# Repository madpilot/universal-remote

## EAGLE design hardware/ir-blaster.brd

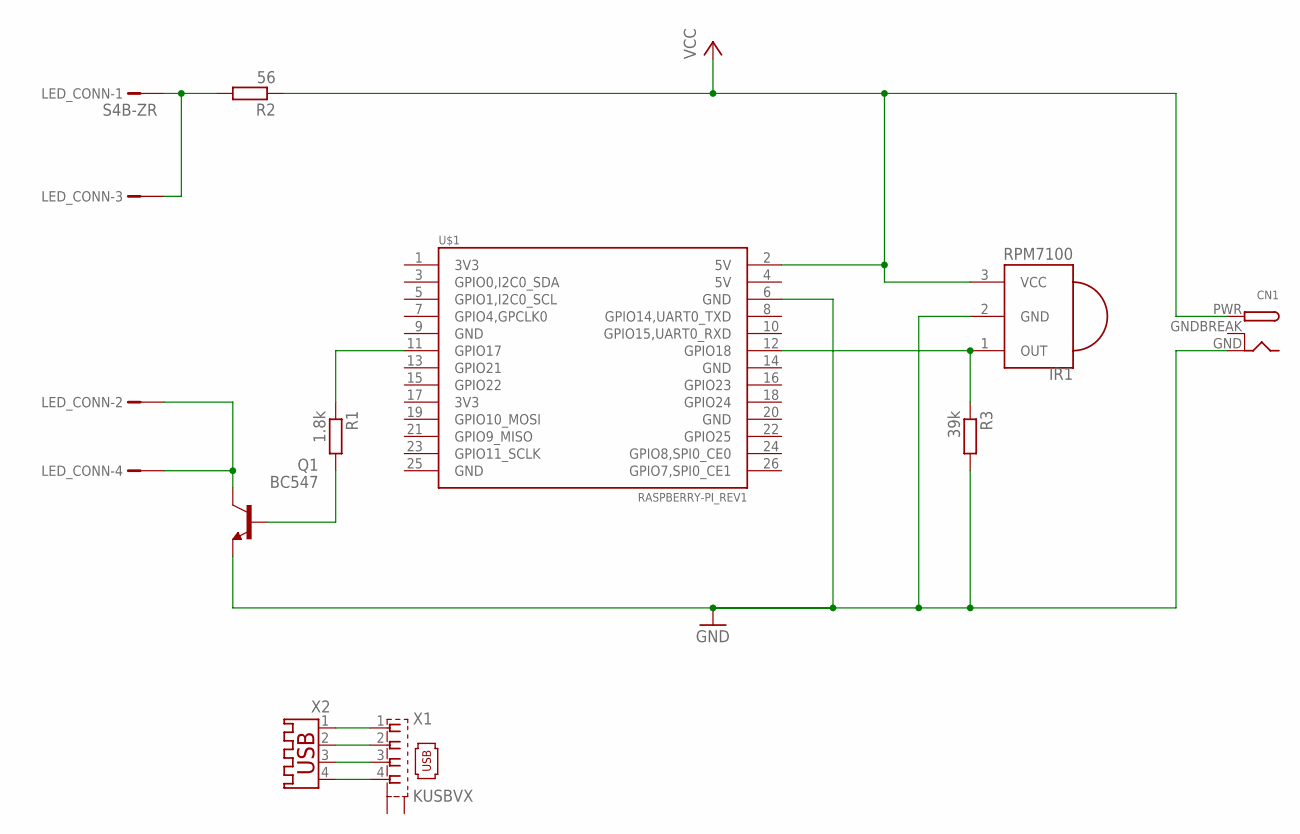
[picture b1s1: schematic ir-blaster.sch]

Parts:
CN1: DCBARRELPTH; DCJACK_2MM_PTH
IR1: RPM7100; PNA460XM
LED_CONN: S4B-ZR
Q1: BC547; TO92
R1: 1.8k; 0207/10
R2: 56; 0207/10
R3: 39k; 0207/10
U$1: RASPBERRY-PI_REV1
X1: KUSBVX
X2: USB-A003

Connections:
GND: CN1.GND, IR1.2 (GND), Q1.1 (E), R3.2, U$1.6 (GND)
GNDBREAK: CN1.GNDBREAK
unnamed: LED_CONN.1, LED_CONN.3, R2.2
unnamed: LED_CONN.2, LED_CONN.4, Q1.3 (C)
unnamed: X1.1, X2.1
unnamed: X1.2, X2.2
unnamed: Q1.2 (B), R1.2
unnamed: R1.1, U$1.11 (GPIO17)
unnamed: IR1.1 (OUT), R3.1, U$1.12 (GPIO18)
unnamed: X1.3, X2.3
unnamed: X1.4, X2.4
VCC: CN1.PWR, IR1.3 (VCC), R2.1, U$1.2 (5V)

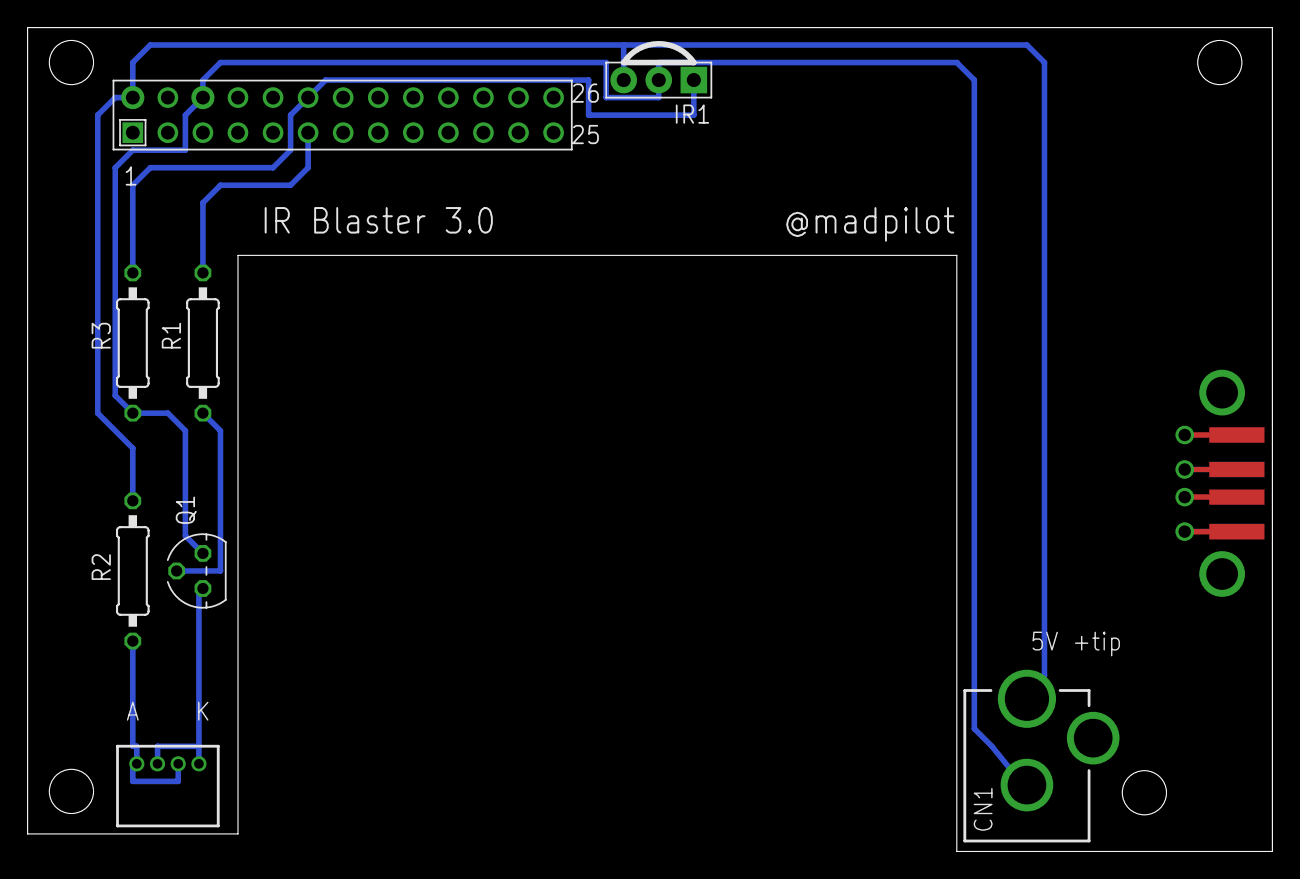
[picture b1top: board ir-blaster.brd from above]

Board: 2 copper layers, 90.2 x 59.7 mm, 10 parts (0 on the bottom side), 11 nets.

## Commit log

2016-01-13 Checking in boards
2016-09-18 Redesigning board so it fits on top of the PI properly
2016-12-05 Building basic device factory
2016-12-05 adding basic http server input
2016-12-05 Adding basic error handling, adding logging
2016-12-05 Logging errors in HTTP Input
2016-12-05 Improving error messages
2016-12-06 adding documents around remote codes
2016-12-06 Adding devices endpoint
2016-12-06 Wrote script to pull codes from CSV
2016-12-07 Adding concept of subscribers, so we can feel back state we read from CEC
2016-12-07 Setting up lirc autodiscovery
2016-12-07 LIRC devices are auto-discovered
2016-12-07 Improving error handling
2016-12-11 Starting work on virtuals
2016-12-12 Adding case STL
2016-12-13 STarting to add CEC stuff
2016-12-13 implementing send, sendstart and sendstop
2016-12-13 CEC changes now run
2016-12-14 CEC works
2016-12-15 Allowing injection of custom scripts to override broken CEC implementations
2017-01-26 Adding support for different winston loggers, moving config.json to config.sample.json
2017-01-26 Adding bin to package.json
2017-01-26 Adding options parser
2017-01-26 Use absolute paths for custom overrides
2017-01-26 Adding a dummy output device for testing
2017-01-27 Adding support for an apiKey
2017-01-28 Building in SSL support
2017-02-26 Revision 3. Moved the LEDs off board onto wires
2017-02-26 Flipping board, so screw holes align of three of the four corners
2017-02-26 Adjusted screw hold position to match ethernet port holes. Reduced width of board so USB network adapter will fit. Adjusted labels to fit on board
2017-02-26 Getting correct measurements for holes. Making the board cover the whole PI again. Added measurement markers for the USB WIFI dongle. Need to make up a custom pad for that
2017-02-27 Adding pads for the USB wifi dongle
2017-06-03 Working on version 3 of the board
2017-06-03 Adding yarn.local
2017-07-16 Removing node server
2017-07-16 Adding a basic phoenix application, and a readme file explaining what is going on
2017-07-16 Setting up the different apps that will be needed
2017-07-20 Adding device and code mappers
2017-07-20 Adding control specs
2017-07-20 Adding tests for reserved
2017-07-23 Basic Genserver sending and receiving data from STDIO
2017-07-23 Using the GenStage module to setup a event bus
2017-07-24 Setup a supervisor trewe with a process and a Genstage producer. Wired up a consumer to test
2017-07-24 Using the BroadcastDispatcher strategy, as the producer is probably the bottle neck
2017-07-24 Cleaning up the Producer init function
2017-07-24 Removing hardcoded executable
2017-07-24 face client captures SIGPIPE
2017-07-25 Testing CEC.Process
2017-07-25 Fixing device identifies, as they are actually only 1 byte, not two
2017-07-26 Starting to implement some command composition
2017-07-26 Adding on_touch_play library
2017-07-26 Adding one_touch_record vanity functions
2017-07-26 Adbstracting away a generic mapper for code translation
2017-07-26 Adding system standby commands
2017-07-26 Adding remote control passthrough
2017-07-27 Adding device menu control
2017-07-27 Adding specs for menu request, status and record error mappings
2017-07-27 Adding audio status
2017-07-27 Adding deck
2017-07-27 Adding deck tests
2017-07-27 Adding in best guess for record on
2017-07-27 Updating readme to better represent where things are going. Not implemented yet though
2017-07-31 Implementing system info
2017-07-31 Using device mappings for report_phsyical_address
2017-07-31 Adding OSD functions
2017-08-02 Adding opcode mappings
2017-08-04 Spliting up source and destination mapping, so parser works correctly
2017-08-04 Renaming opcode -> command, as we'll use that for lirc too
2017-08-04 Started to add argument parsing. needs refactoring
2017-08-05 Mapping abort codes
2017-08-05 Starting to work through testing argument parsers
2017-08-05 Adding more parsers
2017-08-05 Setting up pending test, adding some more parsers
2017-08-05 Testing no argument operands
2017-08-05 More parsers
2017-08-06 Adding parses for audio rate, testing more mapping
2017-08-06 Adding more mapping specs
2017-08-07 Adding a samsung conf, updating the foxtel conf to real values
2017-08-07 Correct foxtel codes
2017-08-08 Adding LIRC setup
2017-08-08 Testing list_devices and list_commands
2017-08-08 Testing send_command
2017-08-09 Putting in specs for op_codes
2017-08-09 Removing phoenix
2017-08-09 Removing the rest of the phoenix config
2017-08-09 Adding plug
2017-08-09 Adding bus command to the packet
2017-08-09 Simple TCP socket. Needs work
2017-08-10 Proof of concept
2017-08-10 Listening to LIRC and CEC bus
2017-08-11 Setting up a remote behaviour that any remote control can implement
2017-08-11 Faking LIRC. Triming output to remove nil objects, adjusting web api to send correct commands, adding a remote behaviour
2017-08-11 Refactoring web api
2017-08-11 ADding a remotes state to maintain a dynamic list of remote controls
2017-08-12 Making naming of remote senders consistant with LIRC, add test for LIRC.remote
2017-08-12 Adding some remote specs
2017-08-13 Testing send commands on CEC remote
2017-08-13 Testing Remotes list
2017-08-13 Testing proxies
2017-08-13 Adding error if a device does not exist for CEC
2017-08-14 Adding key validity check
2017-08-14 Changing error tuple
2017-08-14 More tests on web server
2017-08-15 Using the elixir config system for configuration. Removing json file
2017-08-15 Moving configuration details to correct place, adding some logging
2017-08-15 removing a warning
2017-08-15 Fixing a typo
2017-08-15 Adding more logs
2017-08-17 Adding devices gen_server which can load scripts
2017-08-19 irsend outputs to STDERR in real life
2017-08-19 Working on schema
2017-08-19 Not worrying about config just yet. Cleaned up webserver initialization
2017-08-19 Adding basic process termination
2017-08-23 Adding some tests for devices
2017-08-23 Making commands an actual array
2017-08-26 Adding handler loader
2017-08-27 Refactoring devices to allow send_once, send_start and send_stop
2017-09-10 Need to change the DSL slightly
2017-09-12 Adding tests to the DSL
2018-05-03 Adding status and listeners
2018-05-03 Fixing the filter code
2018-05-03 Testing Bus.wait_for
2018-05-04 Adding status end point
2018-05-04 Rolling back cowboy to verions 1.1.2
2018-05-04 Adding a /status endpoint that returns all possible statuses for a device
2018-05-04 Adding statuses and metadata to /devices/:device
2018-05-04 Supporting CEC version 1.4
2018-05-05 removing ssl, because the RAspberry PI B struggles
2018-05-05 Adding a logger file backend for production
2018-05-06 Moving to a separate bus
2018-05-06 Adding seperate bus. Using receive to sleep the Device - this is literally designed to do what I was hacking around. Extracting the listener, so device can just become a GenServer that delegates bus 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
2018-05-06 Killing the OneShotListener on event timeout
2018-05-07 Bus listener is broker
2018-05-07 Fixing the return result
2018-05-11 Enable fakecec to respond to volume requests
2018-05-19 Adjusting the Listener test
2018-05-19 Testing partial and complete matches
2018-05-19 Testing event listener filter
2018-05-20 Adding an event bus
2018-05-20 Trying again with the unified Bus concept
2018-05-20 Adding some debug to the bus event handler
2018-05-20 Setting up websocket code
2018-05-20 Refactoring device actions out to an API, so websockets can call them too
2018-05-20 Using the new devices API for websockets
2018-05-20 Reformatting
2018-05-20 Adding additional invormation to API responses, so they are more easily identified
2018-05-20 Normalizing the status response
2018-05-20 Adjusting tests to deal with new payload shap. Renaming list_actions to get_metadata
2018-05-20 Fixing a test
2018-05-20 Atomising further up the change, so the API doesn't have to do it
2018-05-20 Abstracting remotes to an API object. Making the API more structured
2018-05-21 Changing top-level bus attribute to channel, to stop clash with the remotes API
2018-05-21 Removing the bus, because it doesn't seem to start listigin properly
2018-05-21 removing some APex.aps
2018-05-21 Gracefully handling bad atom conversion
2018-05-21 Only atomising params is they are strings
2018-05-21 Caching lirc atoms on startup so they can be used in requests
2018-05-21 Removing atom load attempt that didn't work
2018-05-21 Improving the error handling from the web server
2018-05-22 Sending notifications when LIRC commands are sent to devices
2018-05-22 Adding a polling function. It is named at the moment, which isn't ideal, but it'll do for the moment
2018-05-25 Renaming meta_data -> metadata
2018-05-28 Renaming metadata in test fixtures
2018-05-28 Adding excoveralls
2018-06-03 Refactoring to allow loading and unloading of devices in one place. WIP
2018-06-04 Adding tests around the filewatcher and loader
2018-06-05 Building file loading and unloading
2018-06-05 Adding some extra error handling
2018-06-05 Always unloading and reload module on file update
2018-06-11 Fixing tests, because I can't spell
2022-03-06 Adding ping handler to stop things breaking
